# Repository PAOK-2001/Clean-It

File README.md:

# Clean-It
## System Summary: What can Clean It do?
Clean it is an automatic vacuum cleaner that has an autonomous mode that mimics the algorithm used by the Roomba™ for ensuring maximum coverage of the space. It also has 4 preprogrammed paths to follow:

1. **Empty room**: Move straight until colliding with wall, upon collision it turns aroud 180° while slightly moving to the side and move straight until colliding again. This will repeat until timer is done.

2. **Spill clean**: Follow a spiral path to ensure thorough cleaning around a specific area.

3. **Battery Test**: This is a system validation tool, it simply sets the motors to full capacity for calibration and testing purposes.

4. **Room Outline**: In this mode, Clean It will detect a wall to its left and follow along its perimeter. It will also turn on concave and convex corners. 

Both the autonomous mode as well as each of the patterns can be set to run for a certain amount of time, which can be entered using the keypad on the lid. Additionally, the patterns have a *Deep Clean* mode in which Clean It will stop between movements to ensure it will stay in place longer.

## How does Clean It work?

Clean It has the following key components that make up its functionality:
- **Limit Switches**: Used to detect collisions with walls.
-  **Proximity sensors**: Infrared sensors that output variable voltage depending on the distance.
- **H-Bridge and motors**: These form the drive train of the system, using PWM to control vacuum at different speeds.
- **Keypad and LCD**: used for IO.
-  **Turbine**: a turbine is needed to create the preassure difference necessary to displace air in the intake.
-  **Power Distribution**: Clean It is powered by 3 18650 cells, however 5V are necessary for many of the above components including the microprocessor, thus a 5V regulator was implemented and screw terminals where used to map all the power lines.

-  **KL25Z Board and GPIO Board**: The brains of this project is NXP's KL25Z Freedom Board. To interface the board with the components screw terminals where routed to the GPIO pins using a copper-etched PCB, ensuring a robust system.

## Deep dive into the code

Clean It was built using the KL25Z Freedom Board. The code is structured in layers of abstraction, first including simple headers to interface the sensors and actuators and then processing this data to understand Clean It's surroundings. The end goal for the sensor abstractions was to have functions that detect collisions (using limit switches) and posible collisions (using proximity) in boolean terms. As for the actuators, the movements of the vacuum where expressed in terms of direction and parameterized using timers.

In managing this layered approach, the final driver code for the vacuum is much less complex, and it also encourages further contribution and personalization from the community.

| Abstraction Level | Description |
| --- | -------- |
| Hardware level  | The necessary registers are configured for each sensor and actuator, forming an *init* function for each component. The actual reading and/or writting to the GPIO pins also occurs here. |
| Data in context | Once the sensors have been interfaced, the data is read and used to trigger *flags* depending on the value. For example, the proximity sensors and limit switches work together to form the collision avoidance system. |
| Route Planning | Finally the processed data can be used to encapsulate the routines the vacuum will perform. |

## Demo Reel

https://youtu.be/Ws9m0iw0h-8

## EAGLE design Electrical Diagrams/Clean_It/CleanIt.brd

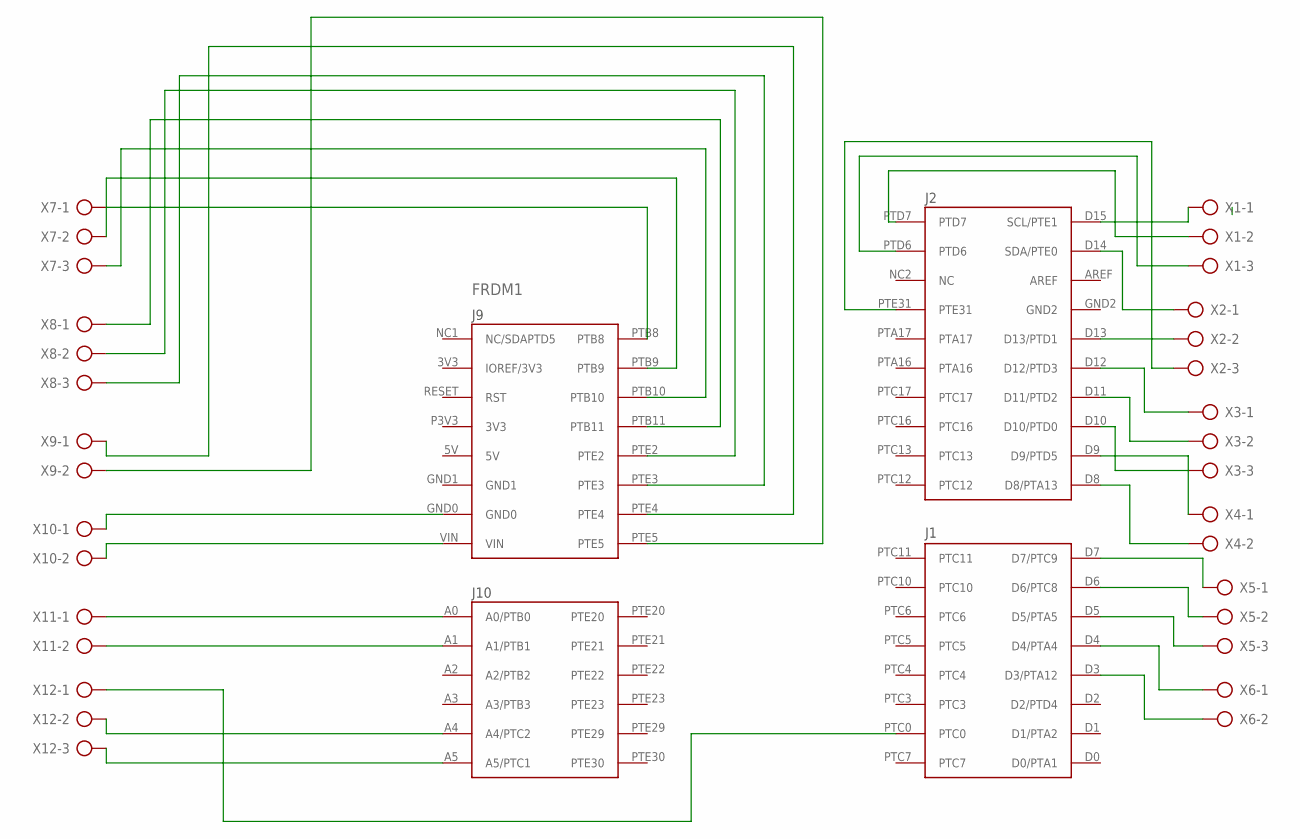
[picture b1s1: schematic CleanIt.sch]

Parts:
FRDM1: FRDM-KL25ZNORMAL; FRDM_KL25Z_NORMAL
X1, X2, X3, X5, X7, X8, X12: AK500/3-H
X4, X6, X9, X10, X11: AK500/2-H

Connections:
unnamed: FRDM1.D15 (SCL/PTE1), X1.1
unnamed: FRDM1.PTD7, X1.2
unnamed: FRDM1.PTD6, X1.3
unnamed: FRDM1.D14 (SDA/PTE0), X2.1
unnamed: FRDM1.D13 (D13/PTD1), X2.2
unnamed: FRDM1.PTE31, X2.3
unnamed: FRDM1.D12 (D12/PTD3), X3.1
unnamed: FRDM1.D11 (D11/PTD2), X3.2
unnamed: FRDM1.D10 (D10/PTD0), X3.3
unnamed: FRDM1.D9 (D9/PTD5), X4.1
unnamed: FRDM1.D8 (D8/PTA13), X4.2
unnamed: FRDM1.D7 (D7/PTC9), X5.1
unnamed: FRDM1.D6 (D6/PTC8), X5.2
unnamed: FRDM1.D5 (D5/PTA5), X5.3
unnamed: FRDM1.D4 (D4/PTA4), X6.1
unnamed: FRDM1.D3 (D3/PTA12), X6.2
unnamed: FRDM1.PTB8, X7.1
unnamed: FRDM1.PTB9, X7.2
unnamed: FRDM1.PTB10, X7.3
unnamed: FRDM1.PTB11, X8.1
unnamed: FRDM1.PTE2, X8.2
unnamed: FRDM1.PTE3, X8.3
unnamed: FRDM1.PTE4, X9.1
unnamed: FRDM1.PTE5, X9.2
unnamed: FRDM1.GND0, X10.1
unnamed: FRDM1.VIN, X10.2
unnamed: FRDM1.A0 (A0/PTB0), X11.1
unnamed: FRDM1.A1 (A1/PTB1), X11.2
unnamed: FRDM1.PTC0, X12.1
unnamed: FRDM1.A4 (A4/PTC2), X12.2
unnamed: FRDM1.A5 (A5/PTC1), X12.3

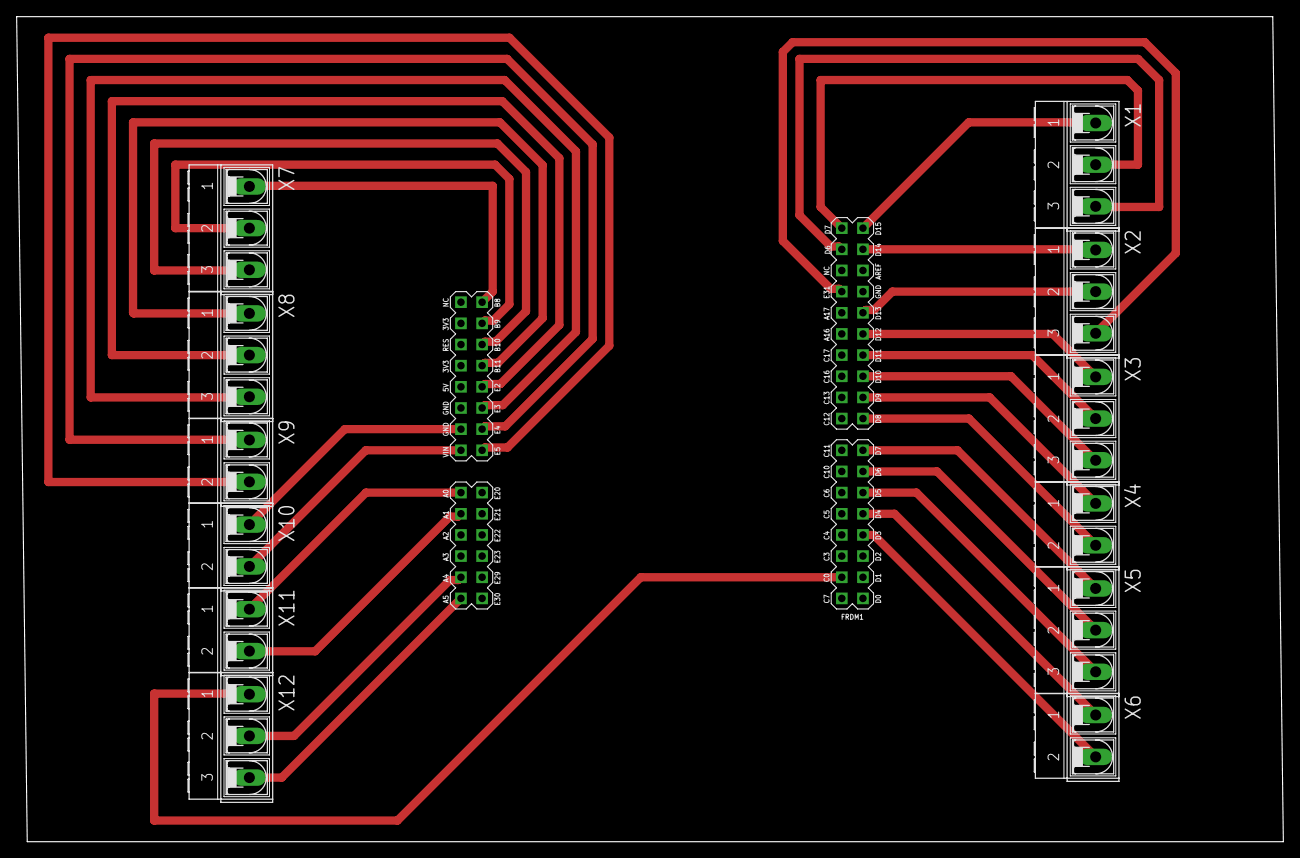
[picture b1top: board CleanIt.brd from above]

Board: 2 copper layers, 152.1 x 99.0 mm, 13 parts (0 on the bottom side), 31 nets.

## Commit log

2022-05-16 Created proyect structure and import headers
2022-05-16 Created protofunctions for proximity sensor header
2022-05-16 Created adc_init function and called it in proximity_init
2022-05-16 Initialized analogue ports in proximity_init
2022-05-16 Completed Proximity_read function, changed its return type to int
2022-05-16 Added driver code
2022-05-17 Adding mbedos
2022-05-17 mbed os
2022-05-17 Updated gitignore
2022-05-17 Added debugging prompt
2022-05-17 Gitignore
2022-05-17 Added averaging to sensor for more accurate results
2022-05-18 Added CM conversion and mbed_app.json for prinf with floats
2022-05-18 Header creation
2022-05-18 hbridge header correction
2022-05-18 Defined menus.h skeleton
2022-05-18 Changed pin assignation in LCD init
2022-05-19 Changed initialization pins in keypad_init()
2022-05-20 Basic code outline
2022-05-20 Implemented collision detection with limit switches
2022-05-20 Implemented collision avoidance methods using switches and proximity
2022-05-21 Implemented predefined cleaning paths
2022-05-22 Added mode selection menu
2022-05-23 Changed delay to be tpm based
2022-05-23 Added get time function
2022-05-23 Fixed commenting
2022-05-23 Added mosfet header
2022-05-24 Fixed mosfet header. Erased mbed.json
2022-05-24 Updated PCB
2022-05-26 Redid PCB in Eagle
2022-05-30 Implemented (UNTESTED): Autonomous routine and components
2022-05-31 Main program and minor adjustments
2022-06-02 Implemented bit masking for correct pin register outputs
2022-06-02 Fixed keypad register mappings
2022-06-03 Fixed typos
2022-06-03 4 bit lcd implementation now works
2022-06-03 Fixed bugs in keypad implementation
2022-06-04 Fixed mosfet issues to the best of our ability
2022-06-04 Fixed typo in function declaration
2022-06-05 Changes after Saturday testing round
2022-06-06 Final changes after Sunday testing
2022-06-06 Adjusted rotation and motor compensation values
2022-06-06 Fixed readme typos
